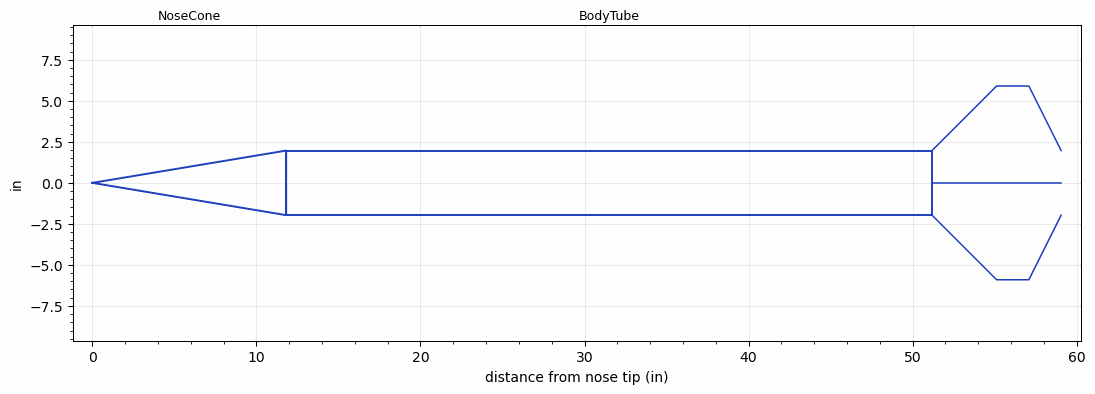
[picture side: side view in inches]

<RASAeroDocument>
 <FileVersion>2</FileVersion>
 <RocketDesign>
  <NoseCone>
   <Length>11.811</Length>
   <Diameter>3.937</Diameter>
   <Shape>Conical</Shape>
   <Location>0</Location>
  </NoseCone>
  <BodyTube>
   <Length>39.3701</Length>
   <Diameter>3.937</Diameter>
   <Location>11.811</Location>
   <Overhang>7.874</Overhang>
   <Fin>
    <Count>4</Count>
    <Chord>7.874</Chord>
    <Span>3.937</Span>
    <SweepDistance>3.937</SweepDistance>
    <TipChord>1.9685</TipChord>
    <Thickness>0.1968</Thickness>
    <LERadius>0.001</LERadius>
    <Location>0</Location>
    <AirfoilSection>Double Wedge</AirfoilSection>
    <FX1>1</FX1>
    <FX3>1</FX3>
   </Fin>
  </BodyTube>
  <Surface>Polished</Surface>
  <ModifiedBarrowman>False</ModifiedBarrowman>
  <Turbulence>False</Turbulence>
  <UseBooster1>False</UseBooster1>
  <UseBooster2>False</UseBooster2>
 </RocketDesign>
 <LaunchSite>
  <Altitude>4000</Altitude>
  <Pressure>0</Pressure>
  <RodAngle>0.5</RodAngle>
  <RodLength>12</RodLength>
  <Temperature>85</Temperature>
  <WindSpeed>3</WindSpeed>
 </LaunchSite>
 <Recovery>
  <Altitude1>1000</Altitude1>
  <Altitude2>1000</Altitude2>
  <DeviceType1>None</DeviceType1>
  <DeviceType2>None</DeviceType2>
  <Event1>False</Event1>
  <Event2>False</Event2>
  <Size1>1</Size1>
  <Size2>1</Size2>
  <EventType1>None</EventType1>
  <EventType2>None</EventType2>
  <CD1>1.33</CD1>
  <CD2>1.33</CD2>
 </Recovery>
</RASAeroDocument>
